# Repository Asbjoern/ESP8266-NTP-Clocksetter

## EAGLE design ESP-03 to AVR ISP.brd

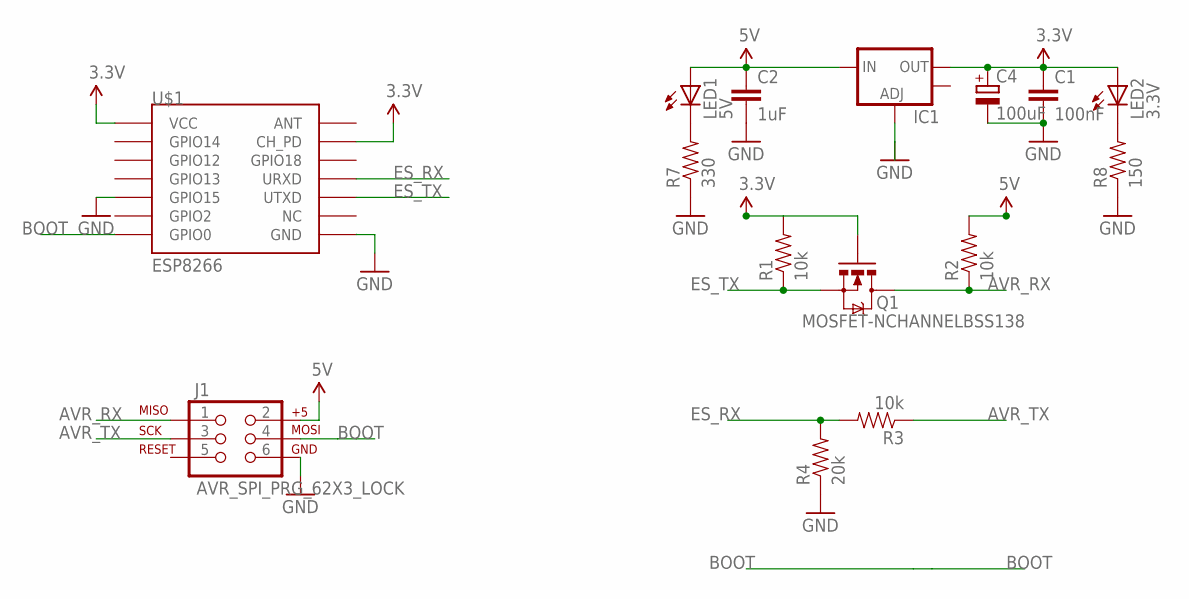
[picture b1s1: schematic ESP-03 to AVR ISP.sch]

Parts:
C1: 100nF; 0603-CAP
C2: 1uF; 0603-CAP
C4: 100uF; B/3528-21R
IC1: V_REG_LM1117SOT223; SOT223
J1: AVR_SPI_PRG_62X3_LOCK; 2X3_LOCK
LED1: 5V; LED-0603
LED2: 3.3V; LED-0603
Q1: MOSFET-NCHANNELBSS138; SOT23-3
R1, R2, R3: 10k; 0603-RES
R4: 20k; 0603-RES
R7: 330; 0603-RES
R8: 150; 0603-RES
U$1: ESP8266; ESP-03

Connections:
3.3V: C1.1, C4.+, IC1.2 (OUT), LED2.A, Q1.1 (G), R1.2, U$1.CH_PD, U$1.VCC
5V: C2.1, IC1.3 (IN), J1.2, LED1.A, R2.2
AVR_RX: J1.1, Q1.3 (D), R2.1
AVR_TX: J1.3, R3.1
BOOT: J1.4, U$1.GPIO0
ES_RX: R3.2, R4.2, U$1.URXD
ES_TX: Q1.2 (S), R1.1, U$1.UTXD
GND: C1.2, C2.2, C4.-, IC1.1 (ADJ), J1.6, R4.1, R7.1, R8.1, U$1.GND, U$1.GPIO15
unnamed: LED1.C, R7.2
unnamed: LED2.C, R8.2

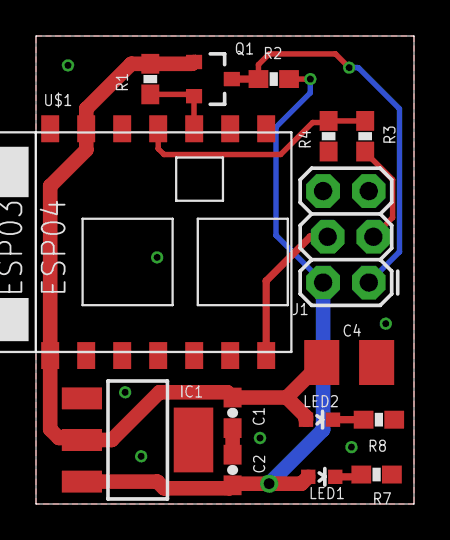
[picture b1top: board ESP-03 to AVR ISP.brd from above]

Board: 2 copper layers, 21.0 x 26.0 mm, 15 parts (0 on the bottom side), 10 nets.

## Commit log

2015-05-12 Add pcb files
2015-05-12 PCB: Fixed wrong VCC connection. Removed Bootloader voltage divider. Changed LDO to 1117type
2015-05-12 Added sourcecode for NTP client that outputs DST time in JSON every hour.
2015-07-23 Fixed PCB. Swithed to 1117 LDO.

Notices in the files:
parts and their libraries:
SparkFun-DiscreteSemi: Licensing: Creative Commons ShareAlike 4.0 International - https://creativecommons.org/licenses/by-sa/4.0
SparkFun-Connectors: Licensing: CC v3.0 Share-Alike You are welcome to use this library for commercial purposes.
